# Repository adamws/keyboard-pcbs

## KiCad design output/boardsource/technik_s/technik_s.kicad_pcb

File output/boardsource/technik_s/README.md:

## boardsource/technik_s

[layout](technik_s-kle.json) - [PCB](technik_s.kicad_pcb)

{:loading="lazy"}

[Open in keyboard-layout-editor](http://www.keyboard-layout-editor.com/##@@_c=#777777;&=0,0&_c=#cccccc;&=0,1&=0,2&=0,3&=0,4&=0,5&=0,6&=0,7&=0,8&=0,9&=0,10&_c=#aaaaaaaa;&=0,11;&@_w:1.5;&=1,0&_c=#cccccc;&=1,2&=1,3&=1,4&=1,5&=1,6&=1,7&=1,8&=1,9&=1,10&_c=#777777&w:1.5;&=1,11;&@_c=#aaaaaaaa;&=2,0&=2,1&_c=#cccccc;&=2,2&=2,3&=2,4&=2,5&=2,6&=2,7&=2,8&=2,9&=2,10&_c=#aaaaaaaa;&=2,11;&@=3,0&=3,1&=3,2&_w:1.5;&=3,3&_c=#777777&w:1.5;&=3,5&_w:1.5;&=3,6&_c=#aaaaaaaa&w:1.5;&=3,8&=3,9&=3,10&=3,11)

{:loading="lazy"}

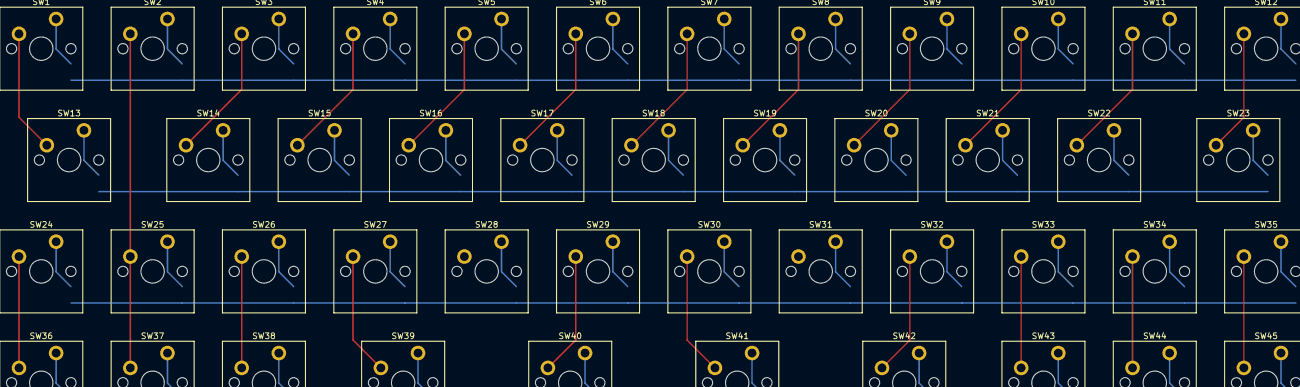
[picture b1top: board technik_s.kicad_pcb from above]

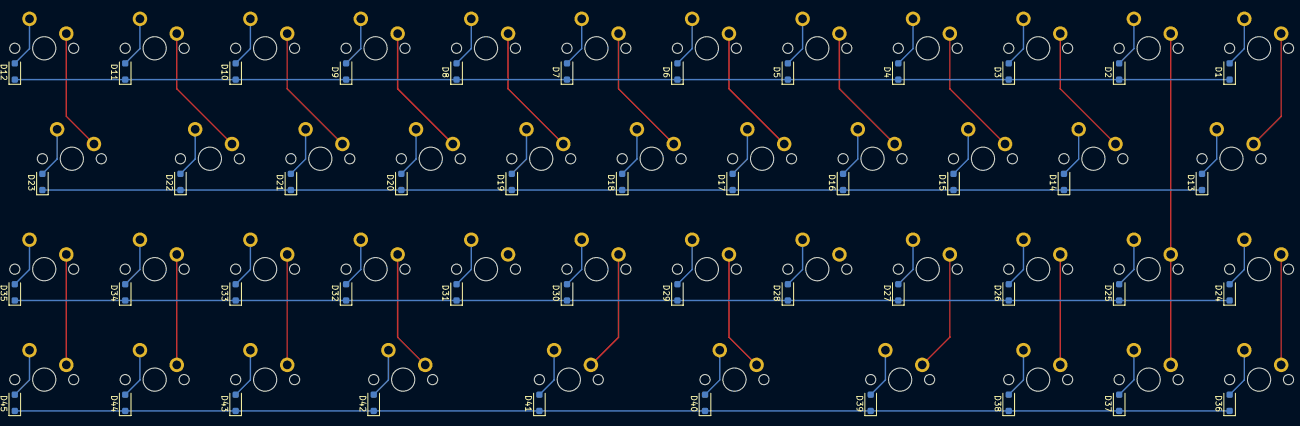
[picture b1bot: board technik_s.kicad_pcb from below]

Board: 2 copper layers, 90 parts (45 on the bottom side), 61 nets.

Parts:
D1, D2, D3, D4, D5, D6, D7, D8, D9, D10, D11, D12, D13, D14, D15, D16, D17, D18, D19, D20, D21, D22, D23, D24, D25, D26, D27, D28, D29, D30, D31, D32, D33, D34, D35, D36, D37, D38, D39, D40, D41, D42, D43, D44, D45: D_SOD-123F
SW1, SW2, SW3, SW4, SW5, SW6, SW7, SW8, SW9, SW10, SW11, SW12, SW13, SW14, SW15, SW16, SW17, SW18, SW19, SW20, SW21, SW22, SW23, SW24, SW25, SW26, SW27, SW28, SW29, SW30, SW31, SW32, SW33, SW34, SW35, SW36, SW37, SW38, SW39, SW40, SW41, SW42, SW43, SW44, SW45: SW_Cherry_MX_PCB_1.00u

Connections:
COL0: SW1.1, SW13.1, SW24.1, SW36.1
COL1: SW2.1, SW25.1, SW37.1
COL2: SW3.1, SW14.1, SW26.1, SW38.1
COL3: SW4.1, SW15.1, SW27.1, SW39.1
COL4: SW5.1, SW16.1, SW28.1
COL5: SW6.1, SW17.1, SW29.1, SW40.1
COL6: SW7.1, SW18.1, SW30.1, SW41.1
COL7: SW8.1, SW19.1, SW31.1
COL8: SW9.1, SW20.1, SW32.1, SW42.1
COL9: SW10.1, SW21.1, SW33.1, SW43.1
COL10: SW11.1, SW22.1, SW34.1, SW44.1
COL11: SW12.1, SW23.1, SW35.1, SW45.1
unnamed: D1.2, SW1.2
unnamed: D2.2, SW2.2
unnamed: D3.2, SW3.2
unnamed: D4.2, SW4.2
unnamed: D5.2, SW5.2
unnamed: D6.2, SW6.2
unnamed: D7.2, SW7.2
unnamed: D8.2, SW8.2
unnamed: D9.2, SW9.2
unnamed: D10.2, SW10.2
unnamed: D11.2, SW11.2
unnamed: D12.2, SW12.2
unnamed: D13.2, SW13.2
unnamed: D14.2, SW14.2
unnamed: D15.2, SW15.2
unnamed: D16.2, SW16.2
unnamed: D17.2, SW17.2
unnamed: D18.2, SW18.2
unnamed: D19.2, SW19.2
unnamed: D20.2, SW20.2
unnamed: D21.2, SW21.2
unnamed: D22.2, SW22.2
unnamed: D23.2, SW23.2
unnamed: D24.2, SW24.2
unnamed: D25.2, SW25.2
unnamed: D26.2, SW26.2
unnamed: D27.2, SW27.2
unnamed: D28.2, SW28.2
unnamed: D29.2, SW29.2
unnamed: D30.2, SW30.2
unnamed: D31.2, SW31.2
unnamed: D32.2, SW32.2
unnamed: D33.2, SW33.2
unnamed: D34.2, SW34.2
unnamed: D35.2, SW35.2
unnamed: D36.2, SW36.2
unnamed: D37.2, SW37.2
unnamed: D38.2, SW38.2
unnamed: D39.2, SW39.2
unnamed: D40.2, SW40.2
unnamed: D41.2, SW41.2
unnamed: D42.2, SW42.2
unnamed: D43.2, SW43.2
unnamed: D44.2, SW44.2
unnamed: D45.2, SW45.2
ROW0: D1.1, D2.1, D3.1, D4.1, D5.1, D6.1, D7.1, D8.1, D9.1, D10.1, D11.1, D12.1
ROW1: D13.1, D14.1, D15.1, D16.1, D17.1, D18.1, D19.1, D20.1, D21.1, D22.1, D23.1
ROW2: D24.1, D25.1, D26.1, D27.1, D28.1, D29.1, D30.1, D31.1, D32.1, D33.1, D34.1, D35.1
ROW3: D36.1, D37.1, D38.1, D39.1, D40.1, D41.1, D42.1, D43.1, D44.1, D45.1

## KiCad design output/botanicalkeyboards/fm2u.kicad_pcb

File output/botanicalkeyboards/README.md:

## botanicalkeyboards/fm2u

[layout](fm2u-kle.json) - [PCB](fm2u.kicad_pcb)

{:loading="lazy"}

[Open in keyboard-layout-editor](http://www.keyboard-layout-editor.com/##@@_c=#777777&w:3&d:true;&=%0A%0A%0A0,0&_w:2;&=0,0%0A%0A%0A0,0&_w:3&d:true;&=%0A%0A%0A0,0;&@_y:0.25&c=#cccccc&w:0.5&d:true;&=%0A%0A%0A0,1&_w:7;&=0,0%0A%0A%0A0,1&_w:0.5&d:true;&=%0A%0A%0A0,1;&@_y:0.25&w:0.9&d:true;&=%0A%0A%0A0,2&_w:6.25;&=0,0%0A%0A%0A0,2&_w:0.8&d:true;&=%0A%0A%0A0,2;&@_y:0.25&d:true;&=%0A%0A%0A0,3&_w:6;&=0,0%0A%0A%0A0,3&_d:true;&=%0A%0A%0A0,3;&@_y:0.25&w:2.5&d:true;&=%0A%0A%0A0,4&_w:3;&=0,0%0A%0A%0A0,4&_w:2.5&d:true;&=%0A%0A%0A0,4;&@_y:0.25&w:2.5&d:true;&=%0A%0A%0A0,5&_c=#aaaaaa&w:2.75;&=0,0%0A%0A%0A0,5&_c=#cccccc&w:2.5&d:true;&=%0A%0A%0A0,5;&@_y:0.25&w:3&d:true;&=%0A%0A%0A0,6&_c=#aaaaaa&w:2.25;&=0,0%0A%0A%0A0,6&_c=#cccccc&w:3&d:true;&=%0A%0A%0A0,6;&@_y:0.25&w:3&d:true;&=%0A%0A%0A0,7&_c=#aaaaaa&w:1.75;&=0,0%0A%0A%0A0,7&_c=#cccccc&w:3&d:true;&=%0A%0A%0A0,7;&@_y:0.25&w:3.25&d:true;&=%0A%0A%0A0,8&_c=#aaaaaa&w:1.5;&=0,0%0A%0A%0A0,8&_c=#cccccc&w:3.25&d:true;&=%0A%0A%0A0,8;&@_y:0.25&w:3.25&d:true;&=%0A%0A%0A0,9&_c=#aaaaaa&w:1.25;&=0,0%0A%0A%0A0,9&_c=#cccccc&w:3.25&d:true;&=%0A%0A%0A0,9;&@_y:0.25&w:3.5&d:true;&=%0A%0A%0A0,10&=0,0%0A%0A%0A0,10&_w:3.5&d:true;&=%0A%0A%0A0,10;&@_y:0.25&c=#777777&w:3&d:true;&=%0A%0A%0A0,11&_x:2&c=#cccccc&w:3&d:true;&=%0A%0A%0A0,11;&@_r:-90&x:-15&y:-11.75&c=#777777&w:1.25&h:2&w2:1.5&h2:1&x2:-0.25;&=0,0%0A%0A%0A0,11)

{:loading="lazy"}

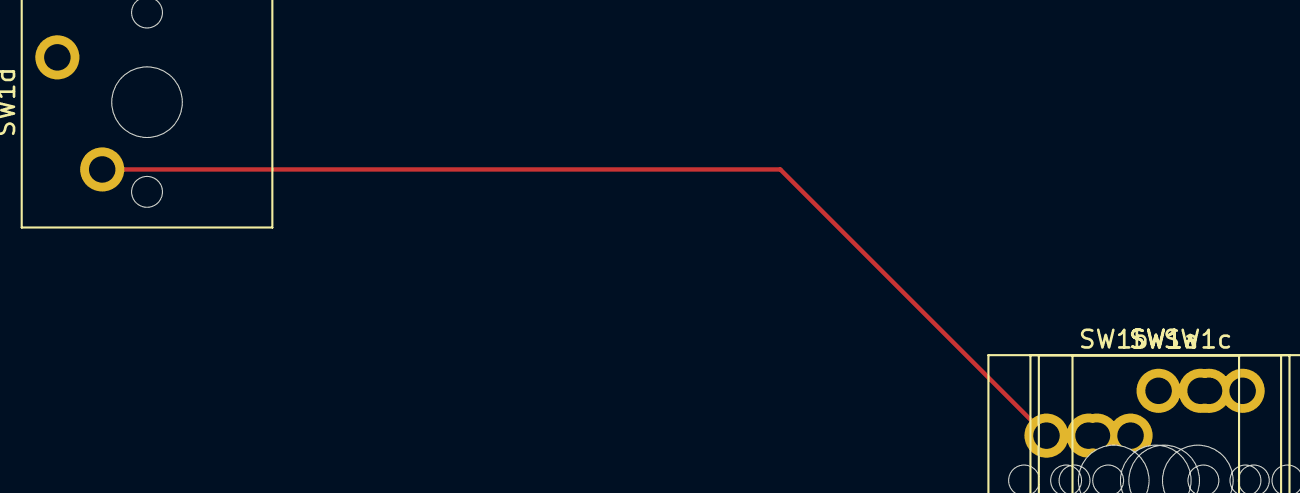
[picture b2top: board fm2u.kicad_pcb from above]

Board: 2 copper layers, 6 parts (1 on the bottom side), 2 nets.

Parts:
D1: D_SOD-123F
SW1, SW1a, SW1b, SW1c, SW1d: SW_Cherry_MX_PCB_1.00u

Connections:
COL0: SW1.1, SW1a.1, SW1b.1, SW1c.1, SW1d.1
unnamed: D1.2, SW1.2, SW1a.2, SW1b.2, SW1c.2, SW1d.2

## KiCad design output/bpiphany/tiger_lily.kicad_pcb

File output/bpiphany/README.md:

## bpiphany/tiger_lily

[layout](tiger_lily-kle.json) - [PCB](tiger_lily.kicad_pcb)

{:loading="lazy"}

[Open in keyboard-layout-editor](http://www.keyboard-layout-editor.com/##@@_x:3&c=#777777;&=6,9&_x:1&c=#cccccc;&=4,8&=4,7&=2,7&=6,7&_x:0.5&c=#aaaaaa;&=7,0&=6,4&=2,3&=4,3&_x:0.5&c=#cccccc;&=4,1&=7,1&=6,1&=0,1&_x:0.25&c=#aaaaaa;&=7,2&=5,2&=5,0;&@_x:3&y:0.5&c=#cccccc;&=4,9&=7,9&=7,8&=7,7&=7,6&=4,6&=4,5&=7,5&=7,4&=7,3&=7,17&=4,17&=4,4&_c=#aaaaaa&w:2;&=2,1&_x:0.25;&=4,11&=4,14&=4,16&_x:0.25&c=#cccccc;&=1,10&=1,11&=1,16&=0,16;&@_x:3&c=#aaaaaa&w:1.5;&=2,9&_c=#cccccc;&=5,9&=5,8&=5,7&=5,6&=2,6&=2,5&=5,5&=5,4&=5,3&=5,17&=2,17&=2,4&_w:1.5;&=3,1%0A%0A%0A0,0&_x:0.25&c=#aaaaaa;&=4,10&=7,14&=7,16&_x:0.25&c=#cccccc;&=5,10&=5,11&=5,16&_h:2;&=5,14;&@_x:3&c=#aaaaaa&w:1.75;&=2,8&_c=#cccccc;&=3,9&=3,8&=3,7&=3,6&=6,6&=6,5&=3,5&=3,4&=3,3&=3,17&=6,17&_c=#777777&w:2.25;&=1,1%0A%0A%0A0,0&_x:3.5&c=#cccccc;&=2,10&=2,11&=2,16;&@_x:3.0&c=#aaaaaa&w:2.25;&=2,13%0A%0A%0A1,0&_c=#cccccc;&=1,9&=1,8&=1,7&=1,6&=0,6&=0,5&=1,5&=1,4&=1,3&=0,17&_c=#aaaaaa&w:2.75;&=3,13&_x:1.25;&=6,14&_x:1.25&c=#cccccc;&=3,10&=3,11&=3,16&_h:2;&=3,14;&@_x:3&c=#aaaaaa&w:1.25;&=4,0&_w:1.25;&=2,15&_w:1.25;&=6,2&_c=#cccccc&w:6.25;&=6,10&_c=#aaaaaa&w:1.25;&=0,2&_w:1.25;&=3,12&_w:1.25;&=0,3&_w:1.25;&=1,0&_x:0.25;&=0,14&=0,10&=0,11&_x:0.25&c=#cccccc&w:2;&=6,11&=6,16;&@_x:27.25&y:-4.0&c=#777777&w:1.25&h:2&w2:1.5&h2:1&x2:-0.25;&=1,1%0A%0A%0A0,1;&@_x:26.25&c=#cccccc;&=3,1%0A%0A%0A0,1;&@_c=#aaaaaa&w:1.25;&=2,13%0A%0A%0A1,1&_c=#cccccc;&=6,8%0A%0A%0A1,1)

{:loading="lazy"}

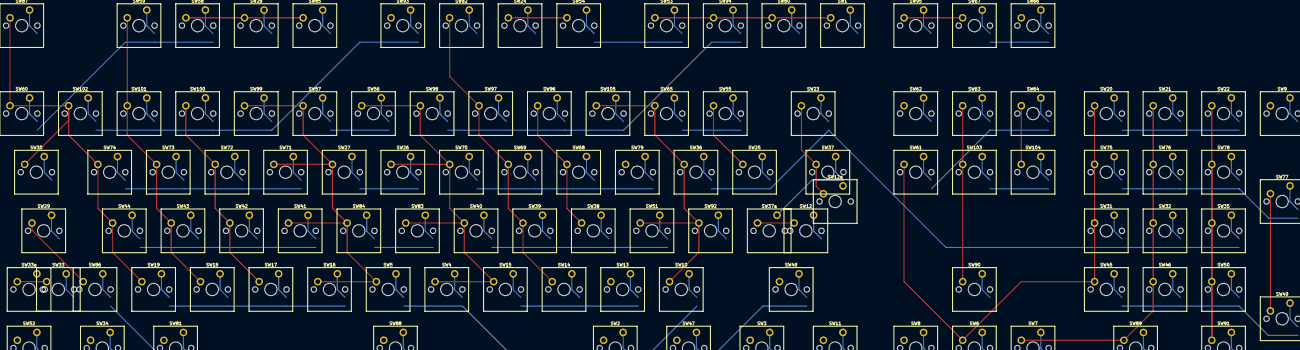
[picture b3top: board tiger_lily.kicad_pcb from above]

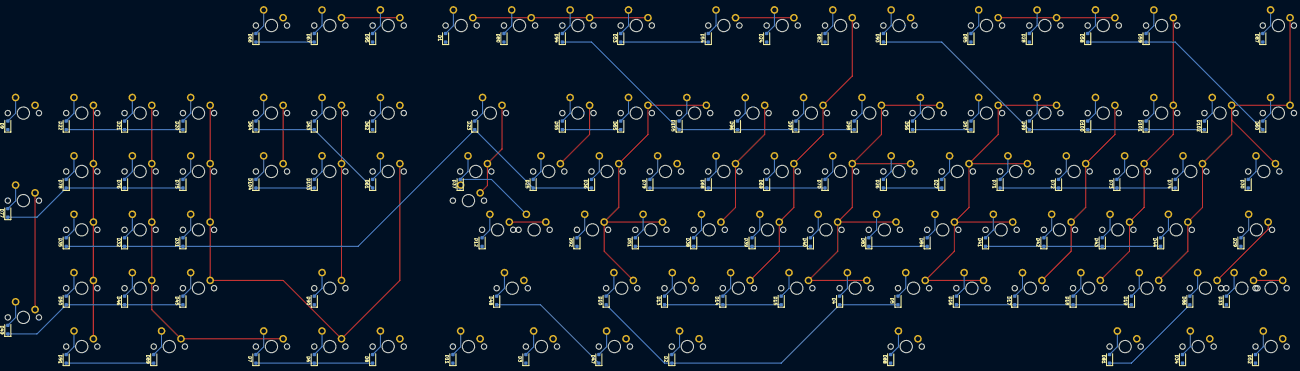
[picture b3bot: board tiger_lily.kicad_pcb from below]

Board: 2 copper layers, 213 parts (105 on the bottom side), 129 nets.

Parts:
D1, D2, D3, D4, D5, D6, D7, D8, D9, D10, D11, D12, D13, D14, D15, D16, D17, D18, D19, D20, D21, D22, D23, D24, D25, D26, D27, D28, D29, D30, D31, D32, D33, D34, D35, D36, D37, D38, D39, D40, D41, D42, D43, D44, D45, D46, D47, D48, D49, D50, D51, D52, D53, D54, D55, D56, D57, D58, D59, D60, D61, D62, D63, D64, D65, D66, D67, D68, D69, D70, D71, D72, D73, D74, D75, D76, D77, D78, D79, D80, D81, D82, D83, D84, D85, D86, D87, D88, D89, D90, D91, D92, D93, D94, D95, D96, D97, D98, D99, D100, D101, D102, D103, D104, D105: D_SOD-123F
SW1, SW2, SW3, SW4, SW5, SW6, SW7, SW8, SW9, SW10, SW11, SW12, SW12a, SW13, SW14, SW15, SW16, SW17, SW18, SW19, SW20, SW21, SW22, SW23, SW24, SW25, SW26, SW27, SW28, SW29, SW30, SW31, SW32, SW33, SW33a, SW34, SW35, SW36, SW37, SW37a, SW38, SW39, SW40, SW41, SW42, SW43, SW44, SW45, SW46, SW47, SW48, SW49, SW50, SW51, SW52, SW53, SW54, SW55, SW56, SW57, SW58, SW59, SW60, SW61, SW62, SW63, SW64, SW65, SW66, SW67, SW68, SW69, SW70, SW71, SW72, SW73, SW74, SW75, SW76, SW77, SW78, SW79, SW80, SW81, SW82, SW83, SW84, SW85, SW86, SW87, SW88, SW89, SW90, SW91, SW92, SW93, SW94, SW95, SW96, SW97, SW98, SW99, SW100, SW101, SW102, SW103, SW104, SW105: SW_Cherry_MX_PCB_1.00u

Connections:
COL0: SW11.1, SW52.1, SW66.1, SW93.1
COL1: SW1.1, SW12.1, SW12a.1, SW23.1, SW37.1, SW37a.1, SW53.1, SW80.1, SW94.1
COL2: SW2.1, SW67.1, SW81.1, SW95.1
COL3: SW3.1, SW13.1, SW24.1, SW38.1, SW54.1, SW68.1, SW96.1
COL4: SW14.1, SW25.1, SW39.1, SW55.1, SW69.1, SW82.1, SW97.1
COL5: SW4.1, SW15.1, SW26.1, SW40.1, SW56.1, SW70.1, SW83.1, SW98.1
COL6: SW5.1, SW16.1, SW27.1, SW41.1, SW57.1, SW71.1, SW84.1, SW99.1
COL7: SW17.1, SW28.1, SW42.1, SW58.1, SW72.1, SW85.1, SW100.1
COL8: SW18.1, SW29.1, SW43.1, SW59.1, SW73.1, SW86.1, SW101.1
COL9: SW19.1, SW30.1, SW44.1, SW60.1, SW74.1, SW87.1, SW102.1
COL10: SW6.1, SW20.1, SW31.1, SW45.1, SW61.1, SW75.1, SW88.1
COL11: SW7.1, SW21.1, SW32.1, SW46.1, SW62.1, SW76.1, SW89.1
COL13: SW33.1, SW33a.1, SW48.1
COL14: SW8.1, SW49.1, SW63.1, SW77.1, SW90.1, SW103.1
COL16: SW9.1, SW22.1, SW35.1, SW50.1, SW64.1, SW78.1, SW91.1, SW104.1
COL17: SW10.1, SW36.1, SW51.1, SW65.1, SW79.1, SW92.1, SW105.1
unnamed: D1.2, SW1.2
unnamed: D2.2, SW2.2
unnamed: D3.2, SW3.2
unnamed: D4.2, SW4.2
unnamed: D5.2, SW5.2
unnamed: D6.2, SW6.2
unnamed: D7.2, SW7.2
unnamed: D8.2, SW8.2
unnamed: D9.2, SW9.2
unnamed: D10.2, SW10.2
unnamed: D11.2, SW11.2
unnamed: D12.2, SW12.2, SW12a.2
unnamed: D13.2, SW13.2
unnamed: D14.2, SW14.2
unnamed: D15.2, SW15.2
unnamed: D16.2, SW16.2
unnamed: D17.2, SW17.2
unnamed: D18.2, SW18.2
unnamed: D19.2, SW19.2
unnamed: D20.2, SW20.2
unnamed: D21.2, SW21.2
unnamed: D22.2, SW22.2
unnamed: D23.2, SW23.2
unnamed: D24.2, SW24.2
unnamed: D25.2, SW25.2
unnamed: D26.2, SW26.2
unnamed: D27.2, SW27.2
unnamed: D28.2, SW28.2
unnamed: D29.2, SW29.2
unnamed: D30.2, SW30.2
unnamed: D31.2, SW31.2
unnamed: D32.2, SW32.2
unnamed: D33.2, SW33.2, SW33a.2
unnamed: D34.2, SW34.2
unnamed: D35.2, SW35.2
unnamed: D36.2, SW36.2
unnamed: D37.2, SW37.2, SW37a.2
unnamed: D38.2, SW38.2
unnamed: D39.2, SW39.2
unnamed: D40.2, SW40.2
unnamed: D41.2, SW41.2
unnamed: D42.2, SW42.2
unnamed: D43.2, SW43.2
unnamed: D44.2, SW44.2
unnamed: D45.2, SW45.2
unnamed: D46.2, SW46.2
unnamed: D47.2, SW47.2
unnamed: D48.2, SW48.2
unnamed: D49.2, SW49.2
unnamed: D50.2, SW50.2
unnamed: D51.2, SW51.2
unnamed: D52.2, SW52.2
unnamed: D53.2, SW53.2
unnamed: D54.2, SW54.2
unnamed: D55.2, SW55.2
unnamed: D56.2, SW56.2
unnamed: D57.2, SW57.2
unnamed: D58.2, SW58.2
unnamed: D59.2, SW59.2
unnamed: D60.2, SW60.2
unnamed: D61.2, SW61.2
unnamed: D62.2, SW62.2
unnamed: D63.2, SW63.2
unnamed: D64.2, SW64.2
unnamed: D65.2, SW65.2
unnamed: D66.2, SW66.2
unnamed: D67.2, SW67.2
unnamed: D68.2, SW68.2
unnamed: D69.2, SW69.2
unnamed: D70.2, SW70.2
unnamed: D71.2, SW71.2
unnamed: D72.2, SW72.2
unnamed: D73.2, SW73.2
unnamed: D74.2, SW74.2
unnamed: D75.2, SW75.2
unnamed: D76.2, SW76.2
unnamed: D77.2, SW77.2
unnamed: D78.2, SW78.2
unnamed: D79.2, SW79.2
unnamed: D80.2, SW80.2
unnamed: D81.2, SW81.2
unnamed: D82.2, SW82.2
unnamed: D83.2, SW83.2
unnamed: D84.2, SW84.2
unnamed: D85.2, SW85.2
unnamed: D86.2, SW86.2
unnamed: D87.2, SW87.2
unnamed: D88.2, SW88.2
unnamed: D89.2, SW89.2
unnamed: D90.2, SW90.2
unnamed: D91.2, SW91.2
unnamed: D92.2, SW92.2
unnamed: D93.2, SW93.2
unnamed: D94.2, SW94.2
unnamed: D95.2, SW95.2
unnamed: D96.2, SW96.2
unnamed: D97.2, SW97.2
unnamed: D98.2, SW98.2
unnamed: D99.2, SW99.2
unnamed: D100.2, SW100.2
unnamed: D101.2, SW101.2
unnamed: D102.2, SW102.2
unnamed: D103.2, SW103.2
unnamed: D104.2, SW104.2
unnamed: D105.2, SW105.2
ROW0: D1.1, D2.1, D3.1, D4.1, D5.1, D6.1, D7.1, D8.1, D9.1, D10.1
ROW1: D11.1, D12.1, D13.1, D14.1, D15.1, D16.1, D17.1, D18.1, D19.1, D20.1, D21.1, D22.1
ROW2: D23.1, D24.1, D25.1, D26.1, D27.1, D28.1, D29.1, D30.1, D31.1, D32.1, D33.1, D34.1, D35.1, D36.1
ROW3: D37.1, D38.1, D39.1, D40.1, D41.1, D42.1, D43.1, D44.1, D45.1, D46.1, D47.1, D48.1, D49.1, D50.1, D51.1
ROW4: D52.1, D53.1, D54.1, D55.1, D56.1, D57.1, D58.1, D59.1, D60.1, D61.1, D62.1, D63.1, D64.1, D65.1
ROW5: D66.1, D67.1, D68.1, D69.1, D70.1, D71.1, D72.1, D73.1, D74.1, D75.1, D76.1, D77.1, D78.1, D79.1
ROW6: D80.1, D81.1, D82.1, D83.1, D84.1, D85.1, D86.1, D87.1, D88.1, D89.1, D90.1, D91.1, D92.1
ROW7: D93.1, D94.1, D95.1, D96.1, D97.1, D98.1, D99.1, D100.1, D101.1, D102.1, D103.1, D104.1, D105.1
